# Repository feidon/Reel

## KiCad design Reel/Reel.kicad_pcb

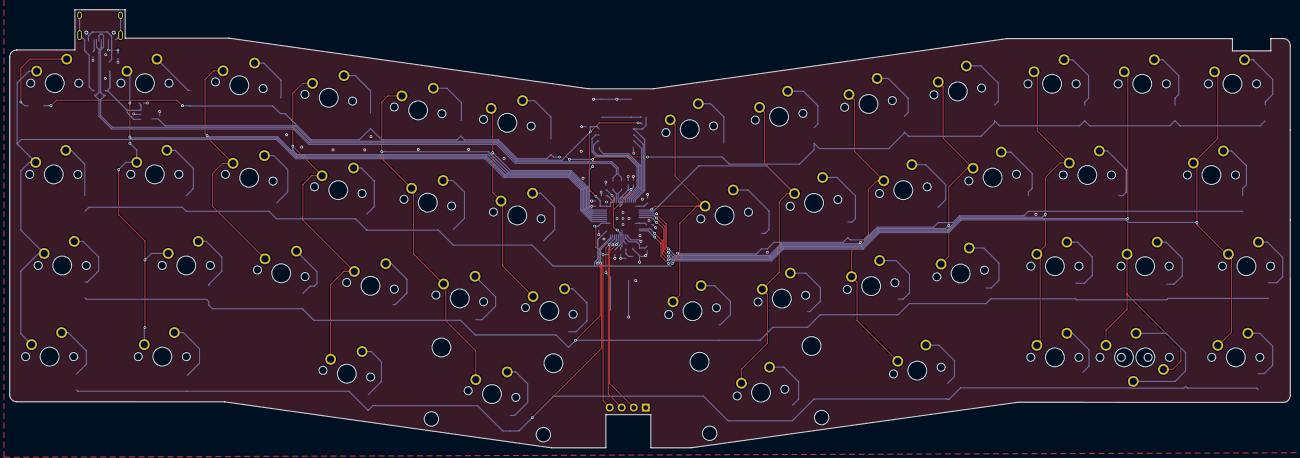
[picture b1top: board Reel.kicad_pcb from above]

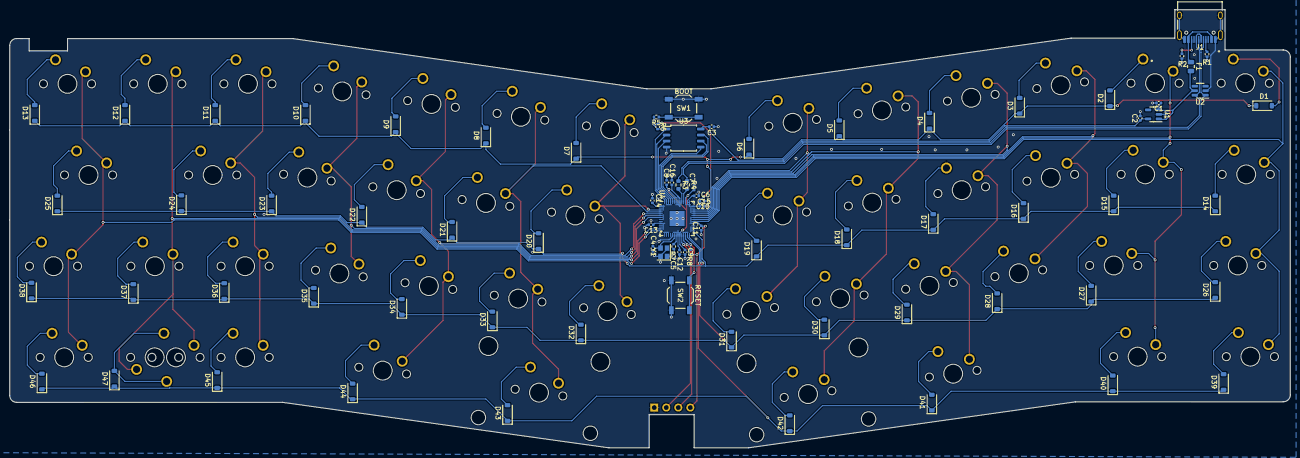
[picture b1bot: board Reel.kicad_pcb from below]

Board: 2 copper layers, 270.4 x 92.5 mm, 129 parts (80 on the bottom side), 88 nets.

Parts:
C1, C2, C6, C7: 1uF; C_0402_1005Metric
C3, C8, C9, C10, C11, C12, C13, C14, C15, C16: 100nF; C_0402_1005Metric
C4, C5: 20pF; C_0402_1005Metric
D1, D2, D3, D4, D5, D6, D7, D8, D9, D10, D11, D12, D13, D14, D15, D16, D17, D18, D19, D20, D21, D22, D23, D24, D25, D26, D27, D28, D29, D30, D31, D32, D33, D34, D35, D36, D37, D38, D39, D40, D41, D42, D43, D44, D45, D46, D47: 1N4148; D_SOD-123
F1: 500mA, 6V; Fuse_0805_2012Metric
J1: USB_C_Receptacle_USB2.0; USB_C_Receptacle_HRO_TYPE-C-31-M-12
J2: NA_Conn_01x04_Female; PinHeader_1x04_P2.54mm_Vertical_debug
KEY1, KEY2, KEY4, KEY5, KEY6, KEY7, KEY8, KEY9, KEY10, KEY11, KEY12, KEY13, KEY15, KEY16, KEY17, KEY18, KEY19, KEY20, KEY21, KEY22, KEY23, KEY24, KEY27, KEY28, KEY29, KEY47: SW_Push_45deg; MX-Solderable-1U
KEY14, KEY48: SW_Push_45deg; MX-Solderable-1.25U
KEY25, KEY26: SW_Push_45deg; MX-Solderable-1.75U
R1, R2: 5.1k; R_0402_1005Metric
R3, R4: 27; R_0603_1608Metric
R5, R7: 1k; R_0402_1005Metric
R6, R8: 10k; R_0402_1005Metric
SW1: BOOT; SW_SPST_TL3342
SW2: RESET; SW_SPST_TL3342
U1: RT9013-33GB; SOT-23-5
U2: SRV05-4; SOT-23-6
U3: W25Q128JVS; SOIC-8_5.23x5.23mm_P1.27mm
U4: RP2040; QFN-56-1EP_7x7mm_P0.4mm_EP3.2x3.2mm
Y1: 12MHz; Crystal_SMD_2520-4Pin_2.5x2.0mm
locked: locked; MX-Solderable-1.25U
locked#2, locked#7, locked#10, locked#16: locked; MX-Solderable-1.25U
locked#3, locked#4, locked#5, locked#6, locked#8, locked#11, locked#13, locked#14, locked#15, locked#17, locked#18: locked; MX-Solderable-1U
locked#9: locked; MX-Solderable-2U-ReversedStabilizers
locked#12: locked; MX-Solderable-2.25U-ReversedStabilizers

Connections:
+1V1: C7.1, C8.1, C9.1, U4.23 (DVDD), U4.45 (VREG_VOUT), U4.50 (DVDD)
+3V3: C2.1, C3.1, C6.1, C10.1, C11.1, C12.1, C13.1, C14.1, C15.1, C16.1, J2.1, R6.1, R8.1, U1.5 (VOUT), U3.8 (VCC), U4.1 (IOVDD), U4.10 (IOVDD), U4.22 (IOVDD), U4.33 (IOVDD), U4.42 (IOVDD), U4.43 (ADC_AVDD), U4.44 (VREG_IN), U4.48 (USB_VDD), U4.49 (IOVDD)
+5V: C1.1, F1.2, U1.1 (VIN), U1.3 (EN), U2.5 (VP)
/RP2040/BOOT: R5.1, SW1.2
/RP2040/QSPI_D0: U3.5 (DI(IO0)), U4.53 (QSPI_SD0)
/RP2040/QSPI_D1: U3.2 (DO(IO1)), U4.55 (QSPI_SD1)
/RP2040/QSPI_D2: U3.3 (IO2), U4.54 (QSPI_SD2)
/RP2040/QSPI_D3: U3.7 (IO3), U4.51 (QSPI_SD3)
/RP2040/QSPI_SCLK: U3.6 (CLK), U4.52 (QSPI_SCLK)
/RP2040/QSPI_SS: R5.2, R6.2, U3.1 (~CS), U4.56 (QSPI_SS)
/RP2040/SWCLK: J2.3, U4.24 (SWCLK)
/RP2040/SWDIO: J2.2, U4.25 (SWD)
/RP2040/~RESET: R8.2, SW2.2, U4.26 (RUN)
/USB_D+: J1.A6 (D+), J1.B6 (D+), R3.1, U2.6 (IO4)
/USB_D-: J1.A7 (D-), J1.B7 (D-), R4.1, U2.1 (IO1)
COL_0: KEY1.1, KEY14.1, KEY26.1, U4.34 (GPIO22), locked#10.1
COL_1: KEY2.1, KEY15.1, KEY27.1, U4.35 (GPIO23), locked#16.1
COL_2: KEY16.1, KEY28.1, U4.36 (GPIO24), locked#13.1
COL_3: KEY4.1, KEY17.1, KEY29.1, U4.37 (GPIO25), locked#7.1
COL_4: KEY5.1, KEY18.1, U4.38 (GPIO26_ADC0), locked#9.1, locked#17.1
COL_5: KEY6.1, KEY19.1, U4.39 (GPIO27_ADC1), locked#11.1
COL_6: KEY7.1, KEY20.1, U4.3 (GPIO1), locked#4.1
COL_7: KEY8.1, KEY21.1, U4.4 (GPIO2), locked#3.1, locked#12.1
COL_8: KEY9.1, KEY22.1, U4.5 (GPIO3), locked#2.1, locked#18.1
COL_9: KEY10.1, KEY23.1, U4.6 (GPIO4), locked#6.1
COL_10: KEY11.1, KEY24.1, U4.7 (GPIO5), locked#8.1, locked#14.1
COL_11: KEY12.1, KEY47.1, KEY48.1, U4.13 (GPIO10), locked#15.1
COL_12: KEY13.1, KEY25.1, U4.14 (GPIO11), locked.1, locked#5.1
GND: C1.2, C2.2, C3.2, C4.1, C5.1, C6.2, C7.2, C8.2, C9.2, C10.2, C11.2, C12.2, C13.2, C14.2, C15.2, C16.2, J1.A1 (GND), J1.A12 (GND), J1.B1 (GND), J1.B12 (GND), J1.S1 (SHIELD), J2.4, R1.2, R2.2, SW1.1, SW2.1, U1.2 (GND), U2.2 (VN), U3.4 (GND), U4.19 (TESTEN), U4.57 (GND), Y1.2, Y1.4
unnamed: C5.2, R7.1, Y1.1
unnamed: D1.2 (A), KEY1.2
unnamed: D2.2 (A), KEY2.2
unnamed: D3.2 (A), locked#13.2
unnamed: D4.2 (A), KEY4.2
unnamed: D5.2 (A), KEY5.2
unnamed: D6.2 (A), KEY6.2
unnamed: D7.2 (A), KEY7.2
unnamed: D8.2 (A), KEY8.2
unnamed: D9.2 (A), KEY9.2
unnamed: D10.2 (A), KEY10.2
unnamed: D11.2 (A), KEY11.2
unnamed: D12.2 (A), KEY12.2
unnamed: D13.2 (A), KEY13.2
unnamed: D14.2 (A), KEY14.2
unnamed: D15.2 (A), KEY15.2
unnamed: D16.2 (A), KEY16.2
unnamed: D17.2 (A), KEY17.2
unnamed: D18.2 (A), KEY18.2
unnamed: D19.2 (A), KEY19.2
unnamed: D20.2 (A), KEY20.2
unnamed: D21.2 (A), KEY21.2
unnamed: D22.2 (A), KEY22.2
unnamed: D23.2 (A), KEY23.2
unnamed: D24.2 (A), KEY24.2
unnamed: D25.2 (A), KEY25.2
unnamed: D26.2 (A), KEY26.2
unnamed: D27.2 (A), KEY27.2
unnamed: D28.2 (A), KEY28.2
unnamed: D29.2 (A), KEY29.2
unnamed: D30.2 (A), locked#17.2
unnamed: D31.2 (A), locked#11.2
unnamed: D32.2 (A), locked#4.2
unnamed: D33.2 (A), locked#3.2
unnamed: D34.2 (A), locked#18.2
unnamed: D35.2 (A), locked#6.2
unnamed: D36.2 (A), locked#8.2
unnamed: D37.2 (A), locked#15.2
unnamed: D38.2 (A), locked.2
unnamed: D39.2 (A), locked#10.2
unnamed: D40.2 (A), locked#16.2
unnamed: D41.2 (A), locked#7.2
unnamed: D42.2 (A), locked#9.2
unnamed: D43.2 (A), locked#12.2
unnamed: D44.2 (A), locked#2.2
unnamed: D45.2 (A), locked#14.2
unnamed: D46.2 (A), locked#5.2
unnamed: D47.2 (A), KEY47.2, KEY48.2
unnamed: J1.A5 (CC1), R1.1
unnamed: J1.B5 (CC2), R2.1
unnamed: R4.2, U4.46 (USB_DM)
unnamed: R3.2, U4.47 (USB_DP)
unnamed: C4.2, U4.20 (XIN), Y1.3
unnamed: R7.2, U4.21 (XOUT)
ROW_0: D1.1 (K), D2.1 (K), D3.1 (K), D4.1 (K), D5.1 (K), D6.1 (K), D7.1 (K), D8.1 (K), D9.1 (K), D10.1 (K), D11.1 (K), D12.1 (K), D13.1 (K), U4.40 (GPIO28_ADC2)
ROW_1: D14.1 (K), D15.1 (K), D16.1 (K), D17.1 (K), D18.1 (K), D19.1 (K), D20.1 (K), D21.1 (K), D22.1 (K), D23.1 (K), D24.1 (K), D25.1 (K), U4.29 (GPIO18)
ROW_2: D26.1 (K), D27.1 (K), D28.1 (K), D29.1 (K), D30.1 (K), D31.1 (K), D32.1 (K), D33.1 (K), D34.1 (K), D35.1 (K), D36.1 (K), D37.1 (K), D38.1 (K), U4.28 (GPIO17)
ROW_3: D39.1 (K), D40.1 (K), D41.1 (K), D42.1 (K), D43.1 (K), D44.1 (K), D45.1 (K), D46.1 (K), D47.1 (K), U4.27 (GPIO16)
VBUS: F1.1, J1.A4 (VBUS), J1.A9 (VBUS), J1.B4 (VBUS), J1.B9 (VBUS)

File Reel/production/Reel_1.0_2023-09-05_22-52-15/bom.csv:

Designator,Footprint,Quantity,Value,LCSC Part #
"C1, C2",0402,2,1µ,C52923
"C10, C11, C12, C13, C14, C15, C16, C3, C8, C9",0402,10,100nF,C307331
"C17, C6, C7",0402,3,1uF,C52923
"C4, C5",0402,2,20pF,C1554
"D1, D10, D11, D12, D13, D14, D15, D16, D17, D18, D19, D2, D20, D21, D22, D23, D24, D25, D26, D27, D28, D29, D3, D30, D31, D32, D33, D34, D35, D36, D37, D38, D39, D4, D40, D41, D42, D43, D44, D45, D46, D5, D6, D7, D8, D9",D_SOD-123,46,1N4148,C81598
F1,0805,1,"500mA, 6V",C269104
J1,USB_C_Receptacle_HRO_TYPE-C-31-M-12,1,USB_C_Receptacle_USB2.0,C165948
J2,PinHeader_1x04_P2.54mm_Vertical_debug,1,NA_Conn_01x04_Female,
"KEY1, KEY10, KEY11, KEY12, KEY13, KEY15, KEY16, KEY17, KEY18, KEY19, KEY2, KEY20, KEY21, KEY22, KEY23, KEY24, KEY27, KEY28, KEY29, KEY3, KEY30, KEY31, KEY32, KEY33, KEY34, KEY35, KEY36, KEY37, KEY4, KEY5, KEY6, KEY7, KEY8, KEY9",MX-Solderable-1U,34,SW_Push_45deg,
"KEY14, KEY38, KEY39, KEY40, KEY41, KEY44, KEY45, KEY46",MX-Solderable-1.25U,8,SW_Push_45deg,
"KEY25, KEY26",MX-Solderable-1.75U,2,SW_Push_45deg,
KEY42,MX-Solderable-2U-ReversedStabilizers,1,SW_Push_45deg,
KEY43,MX-Solderable-2.25U-ReversedStabilizers,1,SW_Push_45deg,
"LED1, LED2",SK6812-MINI-E,2,SK6812,
"R1, R2",0402,2,5.1k,C25905
"R3, R4",0603,2,27,C25190
"R5, R7",0402,2,1k,C11702
"R6, R8",0402,2,10k,C25744
R9,0402,1,330,C11702
SW1,SW_SPST_TL3342,1,BOOT,
SW2,SW_SPST_TL3342,1,RESET,
U1,SOT-23-5,1,RT9013-33GB,C47773
U2,SOT-23-6,1,SRV05-4,C85364
U3,SOIC-8_5.23x5.23mm_P1.27mm,1,W25Q128JVS,C97521
U4,QFN-56-1EP_7x7mm_P0.4mm_EP3.2x3.2mm,1,RP2040,C2040
Y1,Crystal_SMD_2520-4Pin_2.5x2.0mm,1,12MHz,C2149204

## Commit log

2023-08-27 init
2023-09-06 modify git ignore
2023-09-17 multi layout

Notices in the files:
Reel/Reel.kicad_pcb:
MIT License (Open source hardware)
